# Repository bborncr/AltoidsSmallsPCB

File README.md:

# AltoidsSmallsPCB
A simple project to test/practice Kicad 5.0.0.

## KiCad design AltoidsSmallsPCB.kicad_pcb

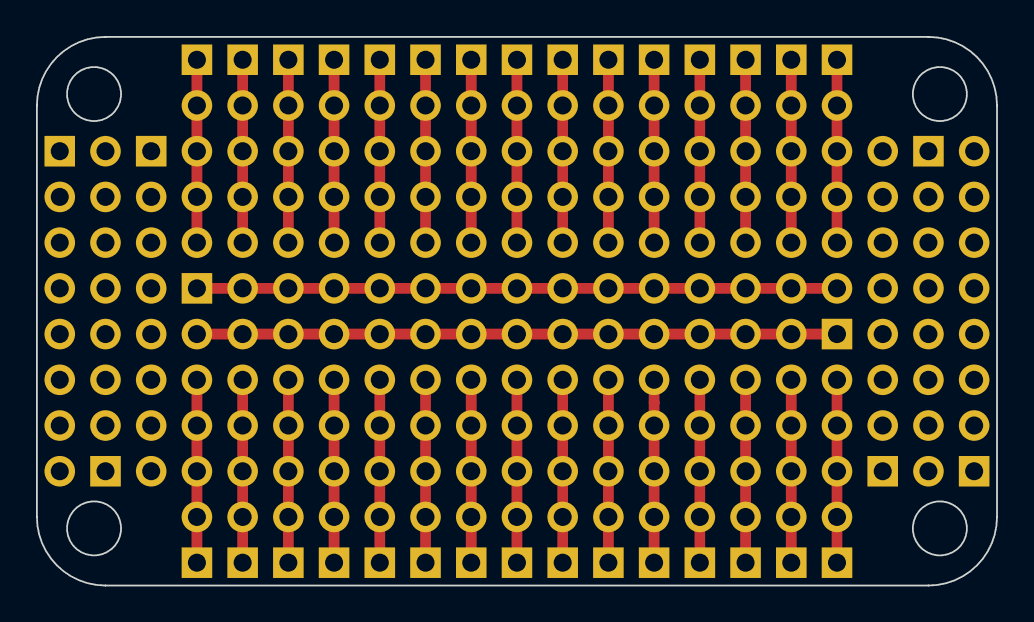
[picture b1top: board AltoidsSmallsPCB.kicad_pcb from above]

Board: 2 copper layers, 53.3 x 30.5 mm, 38 parts (0 on the bottom side), 32 nets.

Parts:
J1, J2, J4, J5, J7, J9, J10, J11, J12, J13, J14, J15, J17, J19, J21, J22, J23, J24, J25, J26, J27, J28, J29, J30, J31, J32, J33, J34, J35, J36: Conn_01x05; Pin_Header_Straight_1x05_Pitch2.54mm
J3, J6, J8, J16, J18, J20: Conn_01x08_Male; Pin_Header_Straight_1x08_Pitch2.54mm
J37, J38: Conn_01x15_Male; Pin_Header_Straight_1x15_Pitch2.54mm

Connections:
GND: J38.1, J38.2, J38.3, J38.4, J38.5, J38.6, J38.7, J38.8, J38.9, J38.10, J38.11, J38.12, J38.13, J38.14, J38.15
unnamed: J1.1, J1.2, J1.3, J1.4, J1.5
unnamed: J2.1, J2.2, J2.3, J2.4, J2.5
unnamed: J4.1, J4.2, J4.3, J4.4, J4.5
unnamed: J5.1, J5.2, J5.3, J5.4, J5.5
unnamed: J7.1, J7.2, J7.3, J7.4, J7.5
unnamed: J9.1, J9.2, J9.3, J9.4, J9.5
unnamed: J10.1, J10.2, J10.3, J10.4, J10.5
unnamed: J11.1, J11.2, J11.3, J11.4, J11.5
unnamed: J12.1, J12.2, J12.3, J12.4, J12.5
unnamed: J13.1, J13.2, J13.3, J13.4, J13.5
unnamed: J14.1, J14.2, J14.3, J14.4, J14.5
unnamed: J15.1, J15.2, J15.3, J15.4, J15.5
unnamed: J17.1, J17.2, J17.3, J17.4, J17.5
unnamed: J19.1, J19.2, J19.3, J19.4, J19.5
unnamed: J21.1, J21.2, J21.3, J21.4, J21.5
unnamed: J22.1, J22.2, J22.3, J22.4, J22.5
unnamed: J23.1, J23.2, J23.3, J23.4, J23.5
unnamed: J24.1, J24.2, J24.3, J24.4, J24.5
unnamed: J25.1, J25.2, J25.3, J25.4, J25.5
unnamed: J26.1, J26.2, J26.3, J26.4, J26.5
unnamed: J27.1, J27.2, J27.3, J27.4, J27.5
unnamed: J28.1, J28.2, J28.3, J28.4, J28.5
unnamed: J29.1, J29.2, J29.3, J29.4, J29.5
unnamed: J30.1, J30.2, J30.3, J30.4, J30.5
unnamed: J31.1, J31.2, J31.3, J31.4, J31.5
unnamed: J32.1, J32.2, J32.3, J32.4, J32.5
unnamed: J33.1, J33.2, J33.3, J33.4, J33.5
unnamed: J34.1, J34.2, J34.3, J34.4, J34.5
unnamed: J35.1, J35.2, J35.3, J35.4, J35.5
unnamed: J36.1, J36.2, J36.3, J36.4, J36.5
VCC: J37.1, J37.2, J37.3, J37.4, J37.5, J37.6, J37.7, J37.8, J37.9, J37.10, J37.11, J37.12, J37.13, J37.14, J37.15
